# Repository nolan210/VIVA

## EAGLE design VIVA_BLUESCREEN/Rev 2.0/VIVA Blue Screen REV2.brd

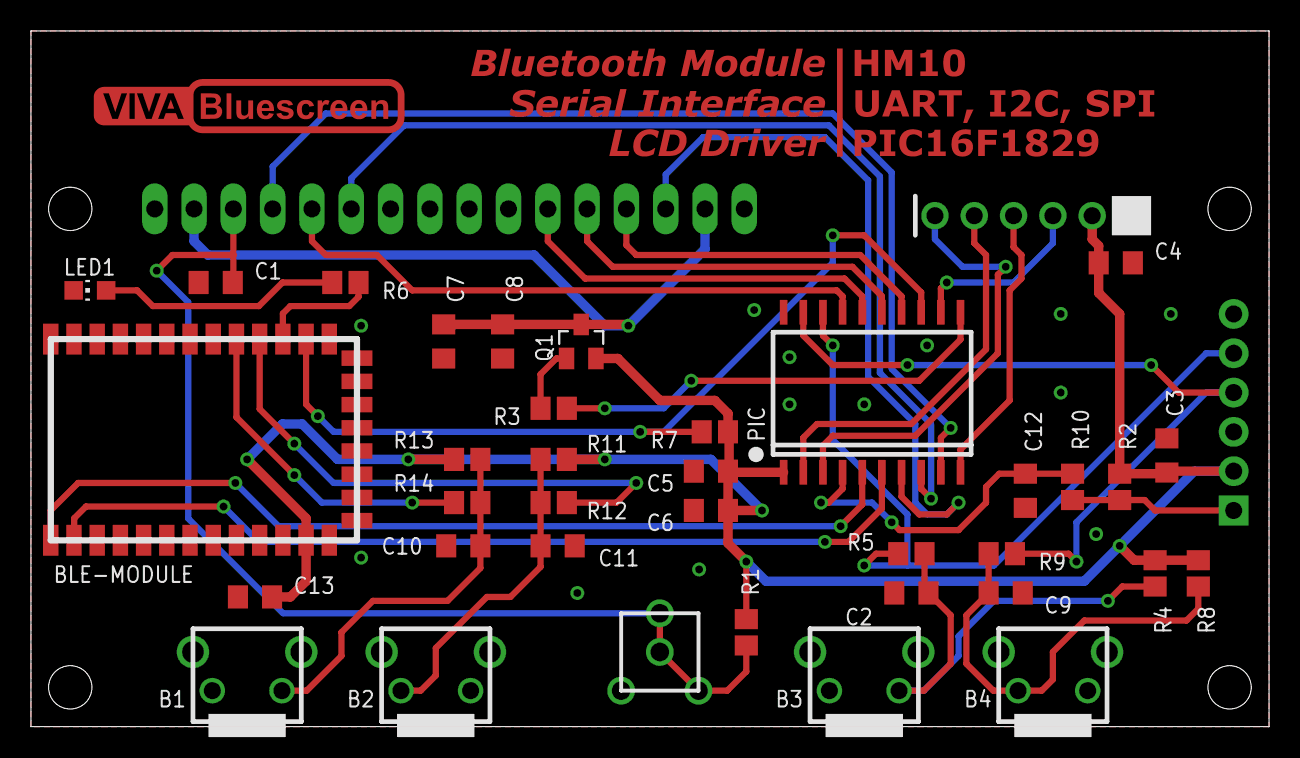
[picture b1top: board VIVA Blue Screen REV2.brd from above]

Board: 2 copper layers, 80.0 x 45.0 mm, 41 parts (1 on the bottom side), 32 nets.

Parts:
B1, B2, B3, B4: 6MM_RA
BLE-MODULE: HM-10; HM-10_EDGE
C1, C3, C7, C13: 4u7; C0805
C2, C9, C12: 100n; C0805
C4, C5, C8, C10, C11: 47n; C0805
C6: 47u; C0805
J3: PICKIT3PLAIN; PINS_6
LED1: CHIP-LED0805
PIC: PIC16F1829; SOP20-NEW
Q1: PNP; SOT23
R1: R0805
R2, R4, R5, R6, R7, R8, R9, R11, R12, R13, R14: 10k; R0805
R3: 100; R0805
R10: 470; R0805
TM1: TRIMER
U$1: PINS_6SILK; PCB_6
U$2: VIVA_BLUESCREEN_LOGO
U$3: VIVA_BLUESCREEN_TEXT
X1: HD44780LCD-1602; LCD1602

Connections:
BLE.RX: BLE-MODULE.2, PIC.6
BLE.SK: BLE-MODULE.23, PIC.13, R7.2
BLE.TX: BLE-MODULE.1, PIC.5
GND: B1.1, B2.2, B3.1, B4.2, BLE-MODULE.13, BLE-MODULE.14, BLE-MODULE.21, BLE-MODULE.22, C1.1, C2.1, C3.1, C4.1, C5.1, C6.1, C7.1, C8.1, C9.1, C10.1, C11.1, C12.1, C13.1, J3.3, LED1.C, PIC.20, TM1.P$1, U$1.P$1, X1.1, X1.16
HM.B1: BLE-MODULE.26, R14.1
HM.B2: BLE-MODULE.25, R12.1
LCD.D4: PIC.16, X1.11
LCD.D5: PIC.15, X1.12
LCD.D6: PIC.14, X1.13
LCD.D7: PIC.7, X1.14
LCD.E: PIC.8, X1.6
LCD.RS: PIC.9, X1.4
LCD.RW: PIC.17, X1.5
LCD_+V: C7.2, C8.2, Q1.3, X1.2, X1.15
LCD_CONTRAST: C1.2, R1.2, TM1.P$2, TM1.P$3, TM1.P$4, X1.3
LCD_CONTROL: PIC.11, R3.1
MCLR: C12.2, PIC.4, R10.2
unnamed: BLE-MODULE.24, R6.2
unnamed: LED1.A, R6.1
unnamed: Q1.1, R3.2
unnamed: B3.2, C2.2, R4.2, R5.2
unnamed: B2.1, C11.2, R11.2, R12.2
unnamed: B1.2, C10.2, R13.2, R14.2
unnamed: J3.1, R2.1, R10.1
unnamed: B4.1, C9.2, R8.2, R9.2
PGC: J3.5, PIC.18, R5.1
PGD: J3.4, PIC.19, R9.1
VDD: BLE-MODULE.12, C3.2, C4.2, C5.2, C6.2, C13.2, J3.2, PIC.1, Q1.2, R1.1, R2.2, R4.1, R7.1, R8.1, R11.1, R13.1, U$1.P$2
VIVA.3: PIC.12, U$1.P$3
VIVA.4: PIC.10, U$1.P$4
VIVA.5: PIC.2, U$1.P$5
VIVA.6: PIC.3, U$1.P$6

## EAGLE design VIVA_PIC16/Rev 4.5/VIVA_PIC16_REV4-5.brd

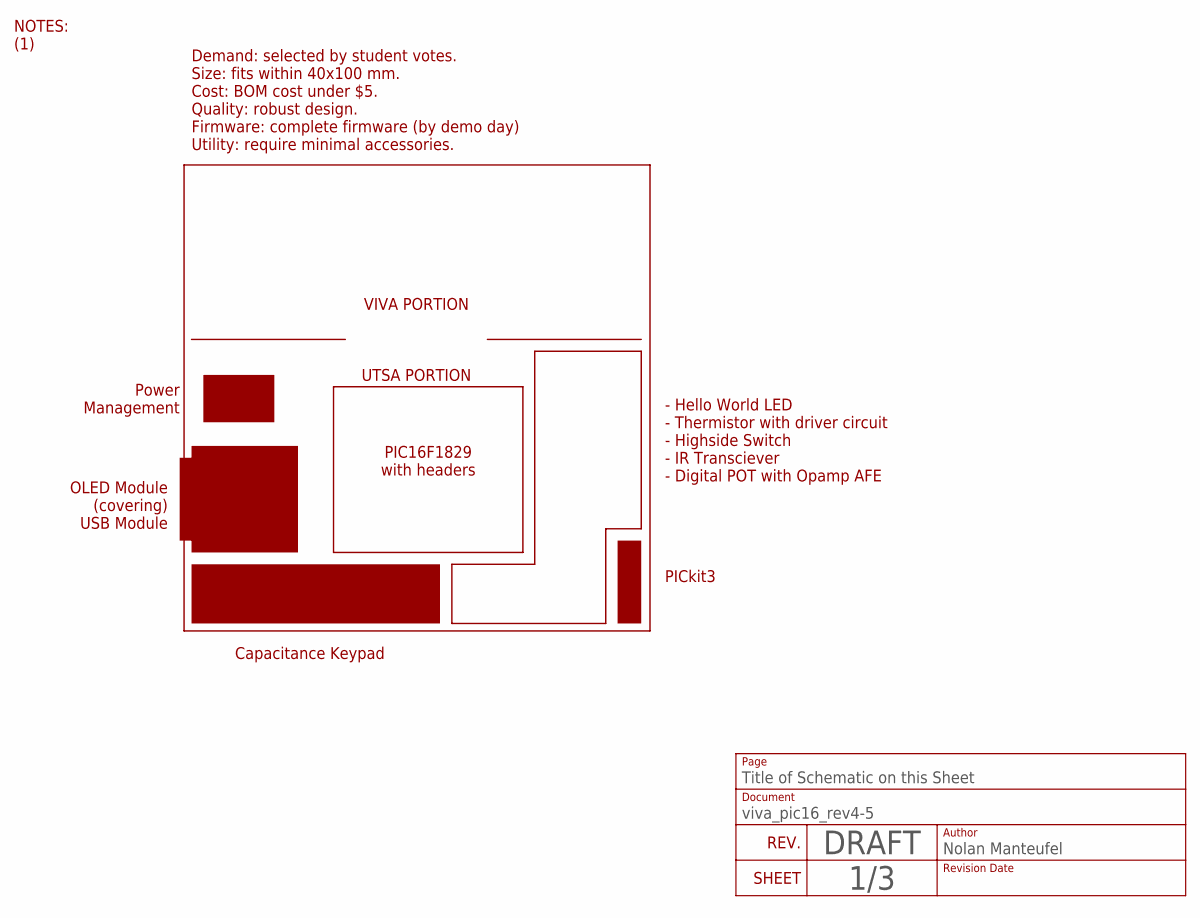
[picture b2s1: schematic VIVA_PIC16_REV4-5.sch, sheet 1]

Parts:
U$1: VIVA_LOGO

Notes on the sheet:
REV.
DRAFT
Revision Date
Author
SHEET
Document
Title of Schematic on this Sheet
Page
Nolan Manteufel
NOTES: (1)
UTSA PORTION
VIVA PORTION
Demand: selected by student votes. Size: fits within 40x100 mm. Cost: BOM cost under $5. Quality: robust design. Firmware: complete firmware (by demo day) Utility: require minimal accessories.
OLED Module (covering) USB Module
Power Management
Capacitance Keypad
PICkit3
PIC16F1829 with headers
- Hello World LED - Thermistor with driver circuit - Highside Switch - IR Transciever - Digital POT with Opamp AFE

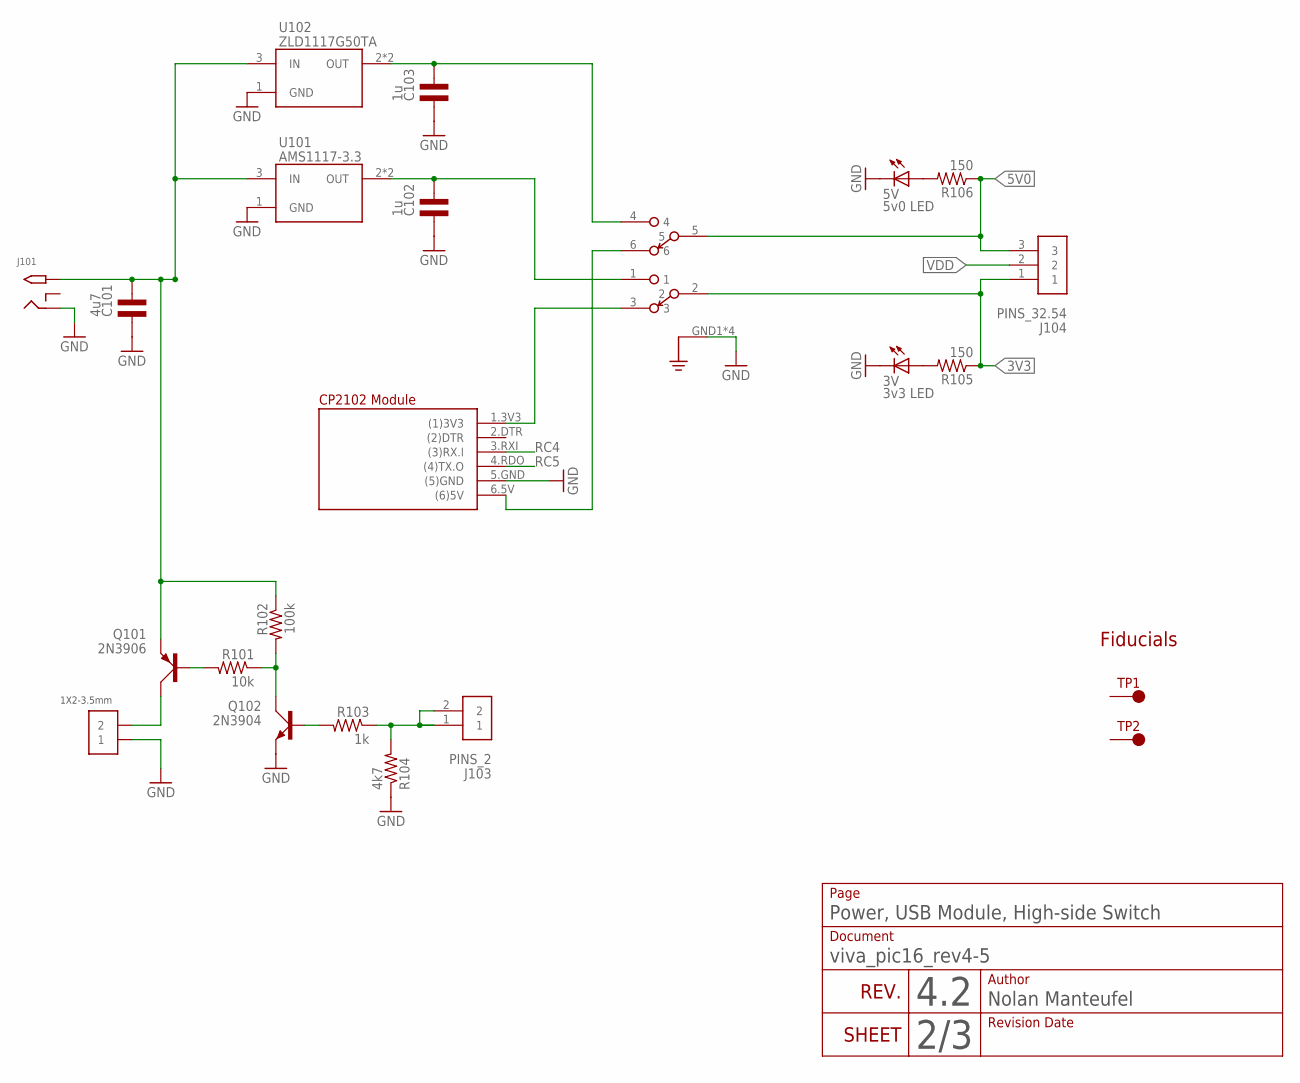
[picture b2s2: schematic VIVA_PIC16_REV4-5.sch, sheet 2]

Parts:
3V: 3v3 LED; CHIPLED_0805
5V: 5v0 LED; CHIPLED_0805
C101: 4u7; C0805
C102, C103: 1u; C0805
J101: 2.1MMJACKTHM; PJ-102A
J102: 1X2-3.5MM-3.5MM; 1X2-3.5MM
J103: PINS_2
J104: PINS_32.54; PINS_3
M101: VIVA_USB-TTL; VIVA_USB_TTL_SUBTEXT
Q101: 2N3906; SOT23
Q102: 2N3904; SOT23
R101: 10k; R0805
R102: 100k; R0805
R103: 1k; R0805
R104: 4k7; R0805
R105, R106: 150; R0805
S101: SWITCH_OS202013; OS202013MT5QN1
TP1, TP2: TESTPOINTFIDUCIAL; FIDUCIAL
U101: AMS1117-3.3; SOT223
U102: ZLD1117G50TA; SOT223

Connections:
3V3: J104.1, R105.1, S101.2
5V0: J104.3, R106.1, S101.5
GND: 3V.C, 5V.C, C101.1, C102.1, C103.1, J101.RING, J102.1, M101.5.GND ((5)GND), Q102.2 (E), R104.1, S101.GND1 (GND), S101.GND2 (GND), S101.GND3 (GND), S101.GND4 (GND), U101.1 (GND), U102.1 (GND); also elsewhere on the board
unnamed: J103.1, J103.2, R103.1, R104.2
unnamed: 5V.A, R106.2
unnamed: Q101.1 (B), R101.2
unnamed: Q102.3 (C), R101.1, R102.2
unnamed: Q102.1 (B), R103.2
unnamed: M101.1.3V3 ((1)3V3), S101.3
unnamed: J102.2, Q101.3 (C)
unnamed: M101.6.5V ((6)5V), S101.6
unnamed: C103.2, S101.4, U102.2 (OUT), U102.4.TAB (OUT)
unnamed: C102.2, S101.1, U101.2 (OUT), U101.4.TAB (OUT)
unnamed: 3V.A, R105.2
RC4: M101.3.RXI ((3)RX.I); also elsewhere on the board
RC5: M101.4.RDO ((4)TX.O); also elsewhere on the board
VDC: C101.2, J101.TIP, Q101.2 (E), R102.1, U101.3 (IN), U102.3 (IN)
VDD: J104.2; also elsewhere on the board

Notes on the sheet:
REV.
4.2
Revision Date
Author
SHEET
Document
Power, USB Module, High-side Switch
Page
Nolan Manteufel
Fiducials

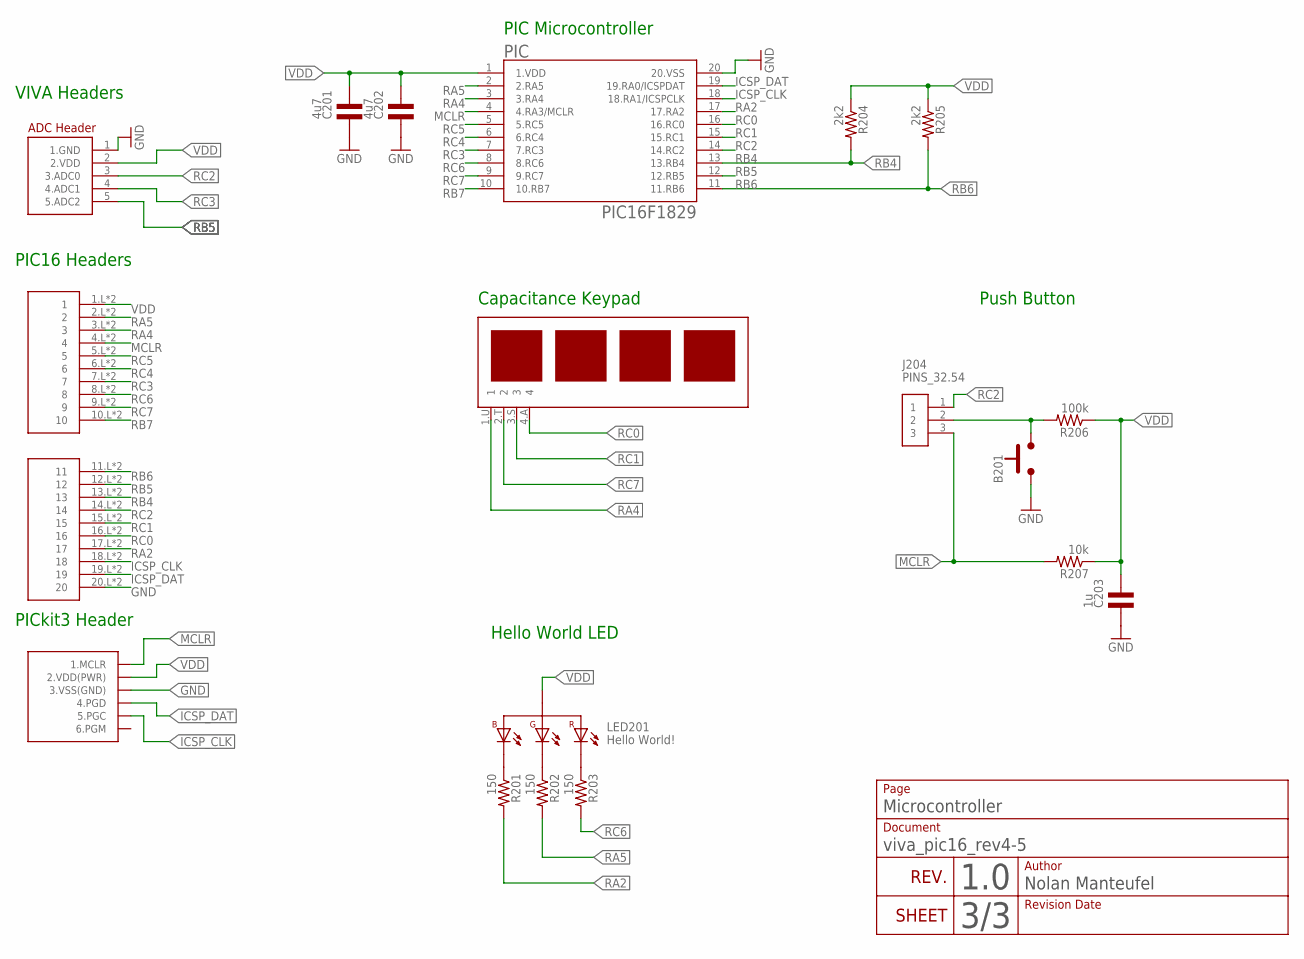
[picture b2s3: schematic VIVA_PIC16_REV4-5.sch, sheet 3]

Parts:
B201: PUSHBUTTON6X6MM; 6X6MM
C201, C202: 4u7; C0805
C203: 1u; C0805
J201: VIVA_PIC16
J202: VIVA-HEADER-ADCNONAME; VIVA-HEADER-ADC-NONAME
J203: PICKIT3
J204: PINS_32.54; PINS_3
LED201: Hello World!; LED_RGB-5050
PIC: PIC16F1829; SOP20-NEW
R201, R202, R203: 150; R0805
R204, R205: 2k2; R0805
R206: 100k; R0805
R207: 10k; R0805
U$201: VIVA_UTSA-KEYPAD

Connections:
GND: B201.1.A (1), B201.2.A (1), C201.1, C202.1, C203.1, J201.20.L (20), J201.20.R (20), J202.1 (1.GND), J203.3 (3.VSS(GND)), PIC.20 (20.VSS); also elsewhere on the board
ICSP_CLK: J201.18.L (18), J201.18.R (18), J203.5 (5.PGC), PIC.18 (18.RA1/ICSPCLK)
ICSP_DAT: J201.19.L (19), J201.19.R (19), J203.4 (4.PGD), PIC.19 (19.RA0/ICSPDAT)
MCLR: J201.4.L (4), J201.4.R (4), J203.1 (1.MCLR), J204.3, PIC.4 (4.RA3/MCLR), R207.2
unnamed: B201.3.B (2), B201.4.B (2), J204.2, R206.2
unnamed: LED201.4.B-, R201.1
unnamed: LED201.2.G-, R202.1
unnamed: LED201.1.R-, R203.1
RA2: J201.17.L (17), J201.17.R (17), PIC.17 (17.RA2), R201.2
RA4: J201.3.L (3), J201.3.R (3), PIC.3 (3.RA4), U$201.1.U (1)
RA5: J201.2.L (2), J201.2.R (2), PIC.2 (2.RA5), R202.2
RB4: J201.13.L (13), J201.13.R (13), PIC.13 (13.RB4), R204.2
RB5: J201.12.L (12), J201.12.R (12), J202.5 (5.ADC2), PIC.12 (12.RB5)
RB6: J201.11.L (11), J201.11.R (11), PIC.11 (11.RB6), R205.2
RB7: J201.10.L (10), J201.10.R (10), PIC.10 (10.RB7)
RC0: J201.16.L (16), J201.16.R (16), PIC.16 (16.RC0), U$201.4.A (4)
RC1: J201.15.L (15), J201.15.R (15), PIC.15 (15.RC1), U$201.3.S (3)
RC2: J201.14.L (14), J201.14.R (14), J202.3 (3.ADC0), J204.1, PIC.14 (14.RC2)
RC3: J201.7.L (7), J201.7.R (7), J202.4 (4.ADC1), PIC.7 (7.RC3)
RC4: J201.6.L (6), J201.6.R (6), PIC.6 (6.RC4); also elsewhere on the board
RC5: J201.5.L (5), J201.5.R (5), PIC.5 (5.RC5); also elsewhere on the board
RC6: J201.8.L (8), J201.8.R (8), PIC.8 (8.RC6), R203.2
RC7: J201.9.L (9), J201.9.R (9), PIC.9 (9.RC7), U$201.2.T (2)
VDD: C201.2, C202.2, C203.2, J201.1.L (1), J201.1.R (1), J202.2 (2.VDD), J203.2 (2.VDD(PWR)), LED201.3.+, PIC.1 (1.VDD), R204.1, R205.1, R206.1, R207.1; also elsewhere on the board

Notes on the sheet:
REV.
1.0
Revision Date
Author
SHEET
Document
Microcontroller
Page
Nolan Manteufel
Push Button
Hello World LED
PICkit3 Header
PIC Microcontroller
VIVA Headers
PIC16 Headers
Capacitance Keypad

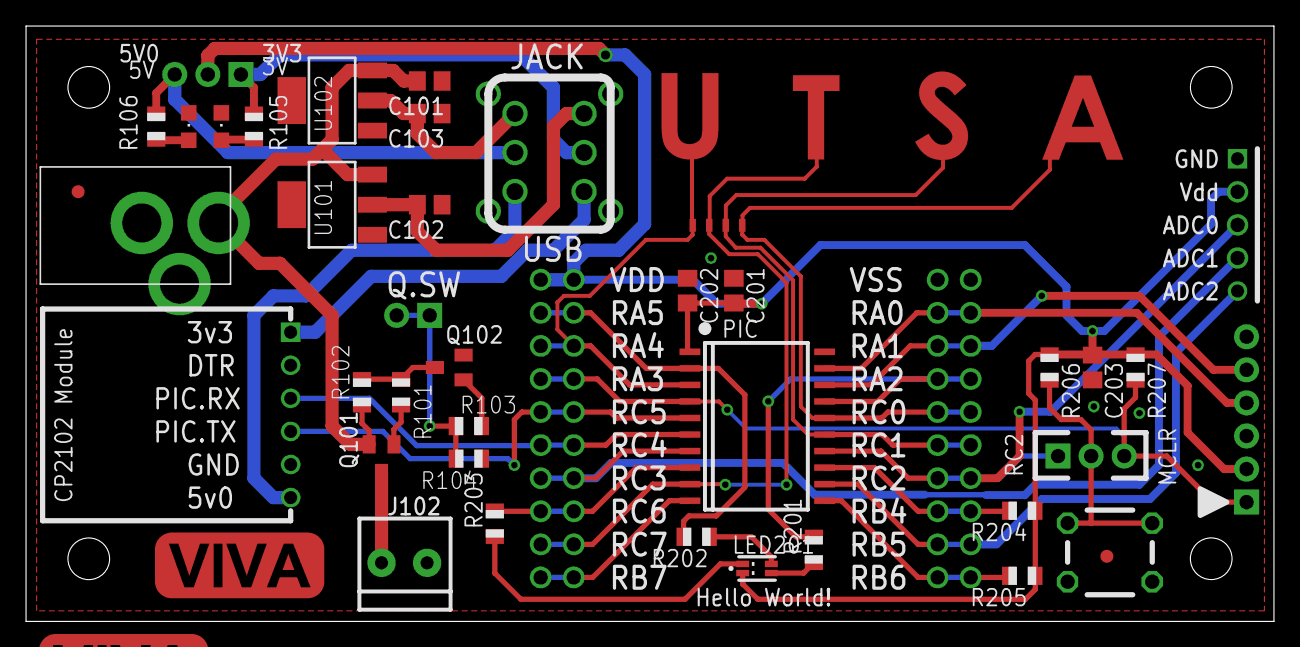
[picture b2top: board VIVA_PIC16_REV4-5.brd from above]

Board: 2 copper layers, 95.8 x 45.7 mm, 43 parts (0 on the bottom side), 38 nets.

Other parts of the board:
U$2: VIVA_LOGO

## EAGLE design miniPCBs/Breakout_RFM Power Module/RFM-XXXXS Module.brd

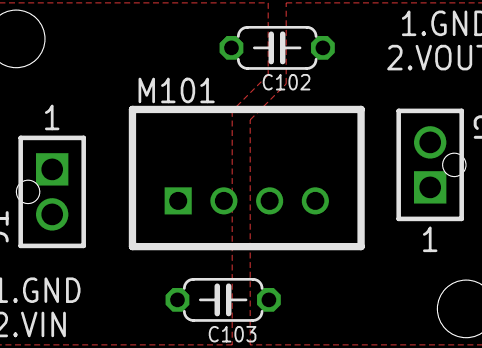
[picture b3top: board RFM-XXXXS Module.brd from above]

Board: 6 copper layers, 5 parts (0 on the bottom side), 4 nets, no tracks yet.

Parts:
C102, C103: 1n 2kV; C050-024X044
J1, J2: PINS_2-NANOFIT-105309-1102; PINS_2-NANOFIT
M101: RFM0505S; RFM-XXXXS

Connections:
0VIN: C103.2, J1.1, M101.1
5V: C102.1, J2.2, M101.4
GND: C103.1, J2.1, M101.3
VIN: C102.2, J1.2, M101.2

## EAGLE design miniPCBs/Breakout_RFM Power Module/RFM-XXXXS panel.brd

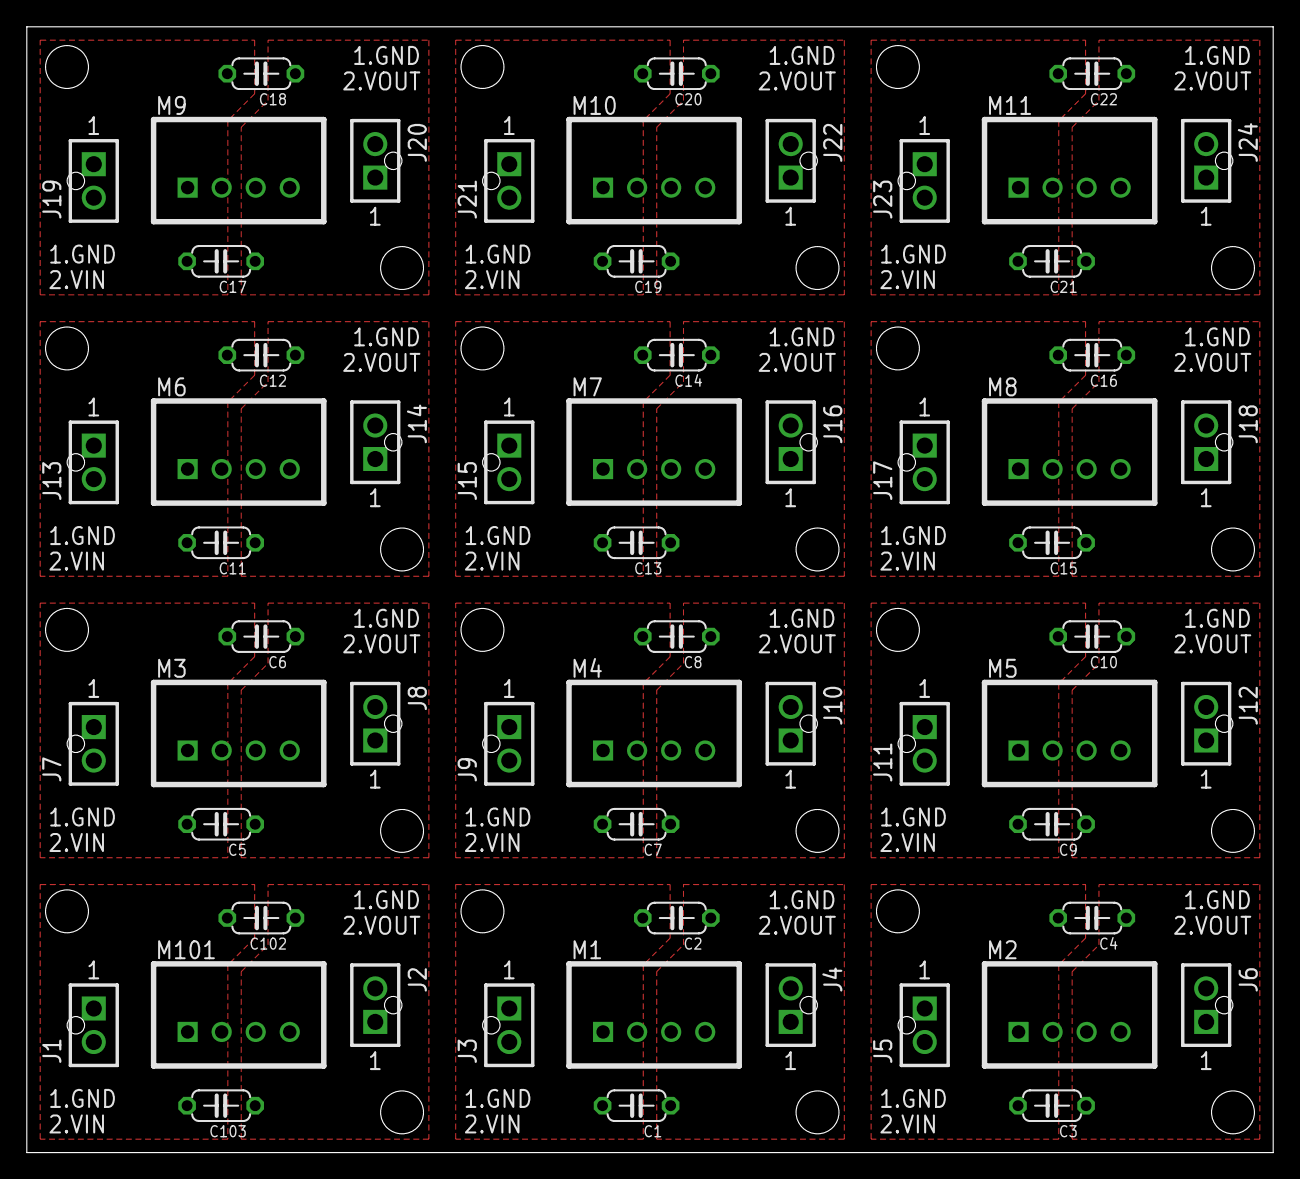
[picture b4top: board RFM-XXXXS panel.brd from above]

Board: 2 copper layers, 93.0 x 84.0 mm, 60 parts (0 on the bottom side), 48 nets, no tracks yet.

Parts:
C1, C2, C3, C4, C5, C6, C7, C8, C9, C10, C11, C12, C13, C14, C15, C16, C17, C18, C19, C20, C21, C22, C102, C103: 1n 2kV; C050-024X044
J1, J2, J3, J4, J5, J6, J7, J8, J9, J10, J11, J12, J13, J14, J15, J16, J17, J18, J19, J20, J21, J22, J23, J24: PINS_2-NANOFIT-105309-1102; PINS_2-NANOFIT
M1, M2, M3, M4, M5, M6, M7, M8, M9, M10, M11, M101: RFM0505S; RFM-XXXXS

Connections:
0VIN: C103.2, J1.1, M101.1
0VIN1: C1.2, J3.1, M1.1
0VIN2: C3.2, J5.1, M2.1
0VIN3: C5.2, J7.1, M3.1
0VIN4: C7.2, J9.1, M4.1
0VIN5: C9.2, J11.1, M5.1
0VIN6: C11.2, J13.1, M6.1
0VIN7: C13.2, J15.1, M7.1
0VIN8: C15.2, J17.1, M8.1
0VIN9: C17.2, J19.1, M9.1
0VIN10: C19.2, J21.1, M10.1
0VIN11: C21.2, J23.1, M11.1
5V: C102.1, J2.2, M101.4
5V1: C2.1, J4.2, M1.4
5V2: C4.1, J6.2, M2.4
5V3: C6.1, J8.2, M3.4
5V4: C8.1, J10.2, M4.4
5V5: C10.1, J12.2, M5.4
5V6: C12.1, J14.2, M6.4
5V7: C14.1, J16.2, M7.4
5V8: C16.1, J18.2, M8.4
5V9: C18.1, J20.2, M9.4
5V10: C20.1, J22.2, M10.4
5V11: C22.1, J24.2, M11.4
GND: C103.1, J2.1, M101.3
GND1: C1.1, J4.1, M1.3
GND2: C3.1, J6.1, M2.3
GND3: C5.1, J8.1, M3.3
GND4: C7.1, J10.1, M4.3
GND5: C9.1, J12.1, M5.3
GND6: C11.1, J14.1, M6.3
GND7: C13.1, J16.1, M7.3
GND8: C15.1, J18.1, M8.3
GND9: C17.1, J20.1, M9.3
GND10: C19.1, J22.1, M10.3
GND11: C21.1, J24.1, M11.3
VIN: C102.2, J1.2, M101.2
VIN1: C2.2, J3.2, M1.2
VIN2: C4.2, J5.2, M2.2
VIN3: C6.2, J7.2, M3.2
VIN4: C8.2, J9.2, M4.2
VIN5: C10.2, J11.2, M5.2
VIN6: C12.2, J13.2, M6.2
VIN7: C14.2, J15.2, M7.2
VIN8: C16.2, J17.2, M8.2
VIN9: C18.2, J19.2, M9.2
VIN10: C20.2, J21.2, M10.2
VIN11: C22.2, J23.2, M11.2

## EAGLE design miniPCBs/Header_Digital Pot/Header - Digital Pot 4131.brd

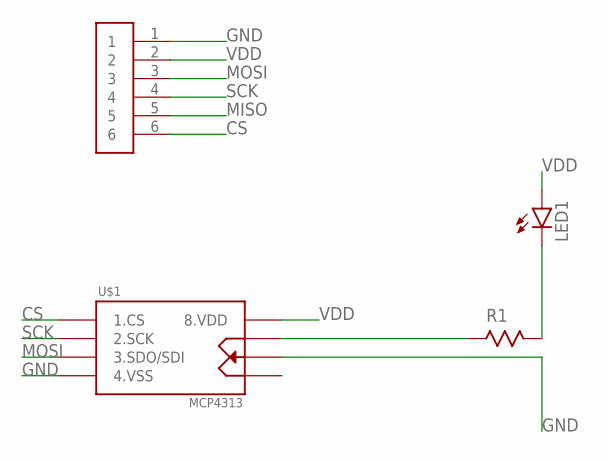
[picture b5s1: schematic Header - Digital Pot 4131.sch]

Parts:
LED1: LED5MM
R1: R204-5; 0204/5
U$1: MCP4131; DIL08
U$2: PINS_6SQUARE; PINS_6

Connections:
CS: U$1.1 (1.CS), U$2.6
GND: U$1.4 (4.VSS), U$1.6 (6.P0W), U$2.1
MISO: U$2.5
MOSI: U$1.3 (3.SDO/SDI), U$2.3
unnamed: LED1.K (C), R1.2
unnamed: R1.1, U$1.7 (7.P0B)
SCK: U$1.2 (2.SCK), U$2.4
VDD: LED1.A, U$1.8 (8.VDD), U$2.2

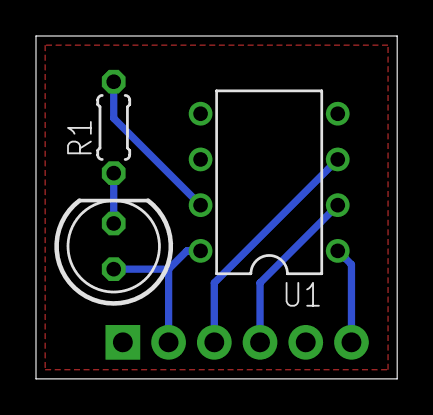
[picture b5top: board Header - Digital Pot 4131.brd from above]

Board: 2 copper layers, 20.1 x 19.1 mm, 4 parts (0 on the bottom side), 7 nets.

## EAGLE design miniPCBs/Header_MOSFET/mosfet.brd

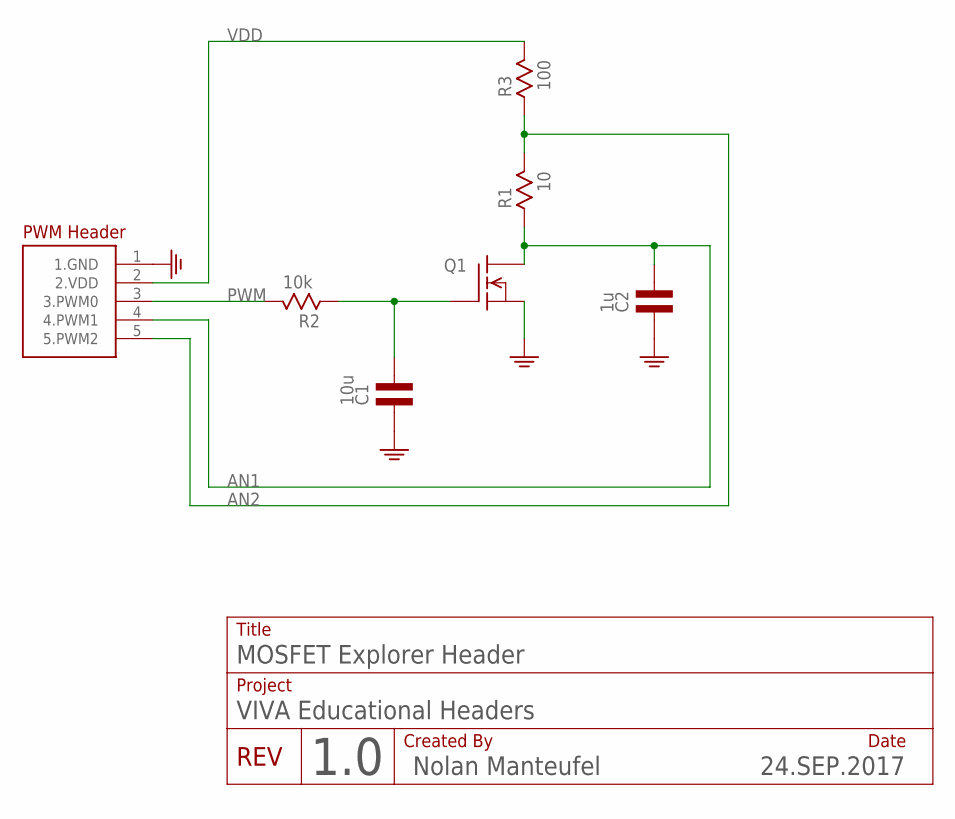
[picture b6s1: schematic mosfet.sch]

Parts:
C1: 10u; C0805
C2: 1u; C0805
Q1: N-MOSFETNX7002AK; SOT23
R1: 10; R0805
R2: 10k; R0805
R3: 100; R0805
U$1: VIVA-HEADER-PWM-XS; PINS_5

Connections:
AN1: C2.2, Q1.3 (D), R1.1, U$1.4 (4.PWM1)
AN2: C1.2, Q1.1 (G), R1.2, R2.1, R3.1, U$1.5 (5.PWM2)
GND: C1.1, C2.1, Q1.2 (S), U$1.1 (1.GND)
PWM: R2.2, U$1.3 (3.PWM0)
VDD: R3.2, U$1.2 (2.VDD)

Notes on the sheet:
VIVA Educational Headers
REV
1.0
Created By
Date
Nolan Manteufel
24.SEP.2017
Project
MOSFET Explorer Header
Title

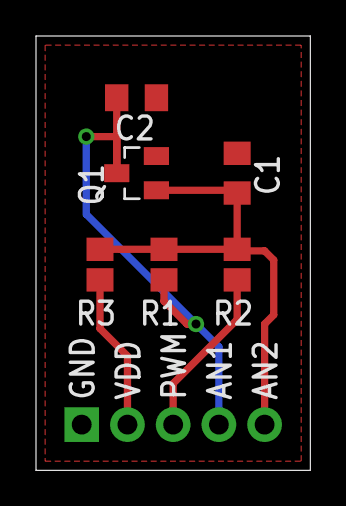
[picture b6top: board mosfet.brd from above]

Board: 2 copper layers, 15.2 x 24.1 mm, 7 parts (0 on the bottom side), 5 nets.

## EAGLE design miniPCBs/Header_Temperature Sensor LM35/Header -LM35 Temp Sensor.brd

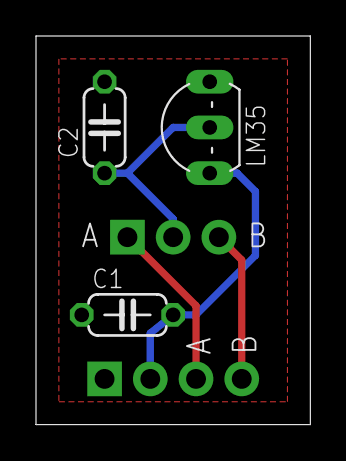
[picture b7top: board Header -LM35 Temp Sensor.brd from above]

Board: 2 copper layers, 15.2 x 21.6 mm, 5 parts (0 on the bottom side), 5 nets.

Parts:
C1, C2: C050-024X044
LM35: LM35; TO92-
U$2: PINS_4
U$3: PINS_3

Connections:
AN1: U$2.3, U$3.1
AN2: U$2.4, U$3.3
GND: C1.1, C2.1, LM35.1, U$2.1
OUTPUT: C2.2, LM35.2, U$3.2
V+: C1.2, LM35.3, U$2.2
